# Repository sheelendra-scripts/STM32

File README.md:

# STM32

Compact STM32F103C8T6 controller board designed in KiCad, with USB power and native USB data lines broken out on PA11/PA12. The design includes on-board 3.3 V regulation, external 16 MHz crystal, filtered analog supply (VDDA), BOOT0 selection, and headers for SWD, UART1, and I2C2. Use it as a reference design or a starting point for custom STM32 hardware.

## Highlights

- Complete KiCad project: schematic, PCB, and project files
- Manufacturing-ready outputs (Gerbers, drill files, and pick-and-place)
- 3D model included for enclosure fit checks

## Preview

### 3D View

### PCB Layout

### PCB Schematic

## What is in this repo

- KiCad source files: schematic, PCB, and project settings
- Mechanical model: STEP file for enclosure alignment
- Manufacturing outputs: Gerbers, drill file, and component placement CSVs
- Reference renders: 3D view, layout, and schematic images

## File labels

| File | Label |
| --- | --- |
| [STM32.kicad_sch](STM32.kicad_sch) | Schematic source |
| [STM32.kicad_pcb](STM32.kicad_pcb) | PCB layout source |
| [STM32.kicad_pro](STM32.kicad_pro) | KiCad project settings |
| [STM32.kicad_prl](STM32.kicad_prl) | KiCad local settings |
| [629105150521 (rev1).stp](629105150521%20(rev1).stp) | 3D mechanical model |
| [3D View.png](3D%20View.png) | 3D render |
| [PCB Layout.png](PCB%20Layout.png) | PCB layout render |
| [PCB Schematic.png](PCB%20Schematic.png) | Schematic render |
| [Manufacturing/STM32.csv](Manufacturing/STM32.csv) | Component list export |
| [Manufacturing/STM32-all-pos.csv](Manufacturing/STM32-all-pos.csv) | Pick-and-place positions |
| [Manufacturing/Gerber/](Manufacturing/Gerber/) | Gerber and drill outputs |
| [README.md](README.md) | Project overview |

## Hardware overview

- Power: USB VBUS into AMS1117-3.3 with bulk input/output caps and a power LED
- Clocking: 16 MHz crystal with load capacitors on HSE
- Boot/reset: BOOT0 SPDT switch, pull resistor, and NRST capacitor
- USB: D+ and D- on PA12/PA11 with 1.5 k pull-up on D+
- Debug: 1x4 SWD header (3.3 V, SWDIO, SWCLK, GND)
- IO headers: UART1 and I2C2 (with pull-ups) on 1x4 headers
- Mechanical: four M2 mounting holes

## Schematic description

- Core MCU: STM32F103C8T6 (U2) with dedicated VDD decoupling (multiple 100 nF caps plus a bulk 10 uF). NRST has a 100 nF cap to ground, and BOOT0 is selectable via a small SPDT switch with a pull resistor.
- Clocking: External 16 MHz crystal (Y1) on HSE_IN/HSE_OUT with two 10 pF load capacitors to ground.
- Power supply: USB VBUS feeds an AMS1117-3.3 LDO with 22 uF input/output caps. A red power LED with a series resistor indicates 3.3 V presence.
- Analog supply filtering: VDDA is isolated from 3.3 V using a ferrite bead and local 10 nF + 1 uF caps, plus a 1 uF cap on VDDA.
- USB interface: Micro-USB connector routes D+/D- to PA12/PA11. A 1.5 k pull-up on D+ provides full-speed identification, with VBUS present for USB power/sense.
- Headers: SWD header with 3.3 V, SWDIO, SWCLK, and GND. UART header (USART1 TX/RX) with 3.3 V and GND. I2C header (I2C2 SCL/SDA) with 3.3 V and GND, plus 1.5 k pull-ups.
- Mechanical: Four M2 mounting holes (H1-H4).

## Bill of materials (BOM)

Values are taken from the schematic. Confirm footprints and ratings before ordering.

| Ref(s) | Qty | Value / Part | Notes |
| --- | --- | --- | --- |
| U2 | 1 | STM32F103C8T6 | LQFP-48 MCU |
| U1 | 1 | AMS1117-3.3 | 5 V to 3.3 V LDO |
| Y1 | 1 | 16 MHz crystal | HSE clock |
| C1, C2 | 2 | 22 uF | LDO input/output bulk |
| C3 | 1 | 10 uF | VDD bulk |
| C4, C5, C6, C7 | 4 | 100 nF | VDD decoupling (one per VDD pin) |
| C8 | 1 | 10 nF | VDDA filter |
| C9, C10 | 2 | 1 uF | VDDA filtering |
| C11 | 1 | 100 nF | NRST cap |
| C12, C13 | 2 | 10 pF | Crystal load caps |
| FB1 | 1 | Ferrite bead, 120 R | VDDA filter |
| D1 | 1 | Red LED | Power indicator |
| R1 | 1 | 1.5 k | LED series resistor |
| R2 | 1 | 10 k | BOOT0 pull |
| R3 | 1 | 1.5 k | USB D+ pull-up |
| R4, R5 | 2 | 1.5 k | I2C pull-ups |
| SW1 | 1 | SPDT switch | BOOT0 select |
| J1 | 1 | Micro-USB B receptacle | USB + power |
| J2 | 1 | 1x4 header | UART1 header |
| J3 | 1 | 1x4 header | SWD header |
| J4 | 1 | 1x4 header | I2C2 header |
| H1, H2, H3, H4 | 4 | M2 mounting holes | Mechanical |

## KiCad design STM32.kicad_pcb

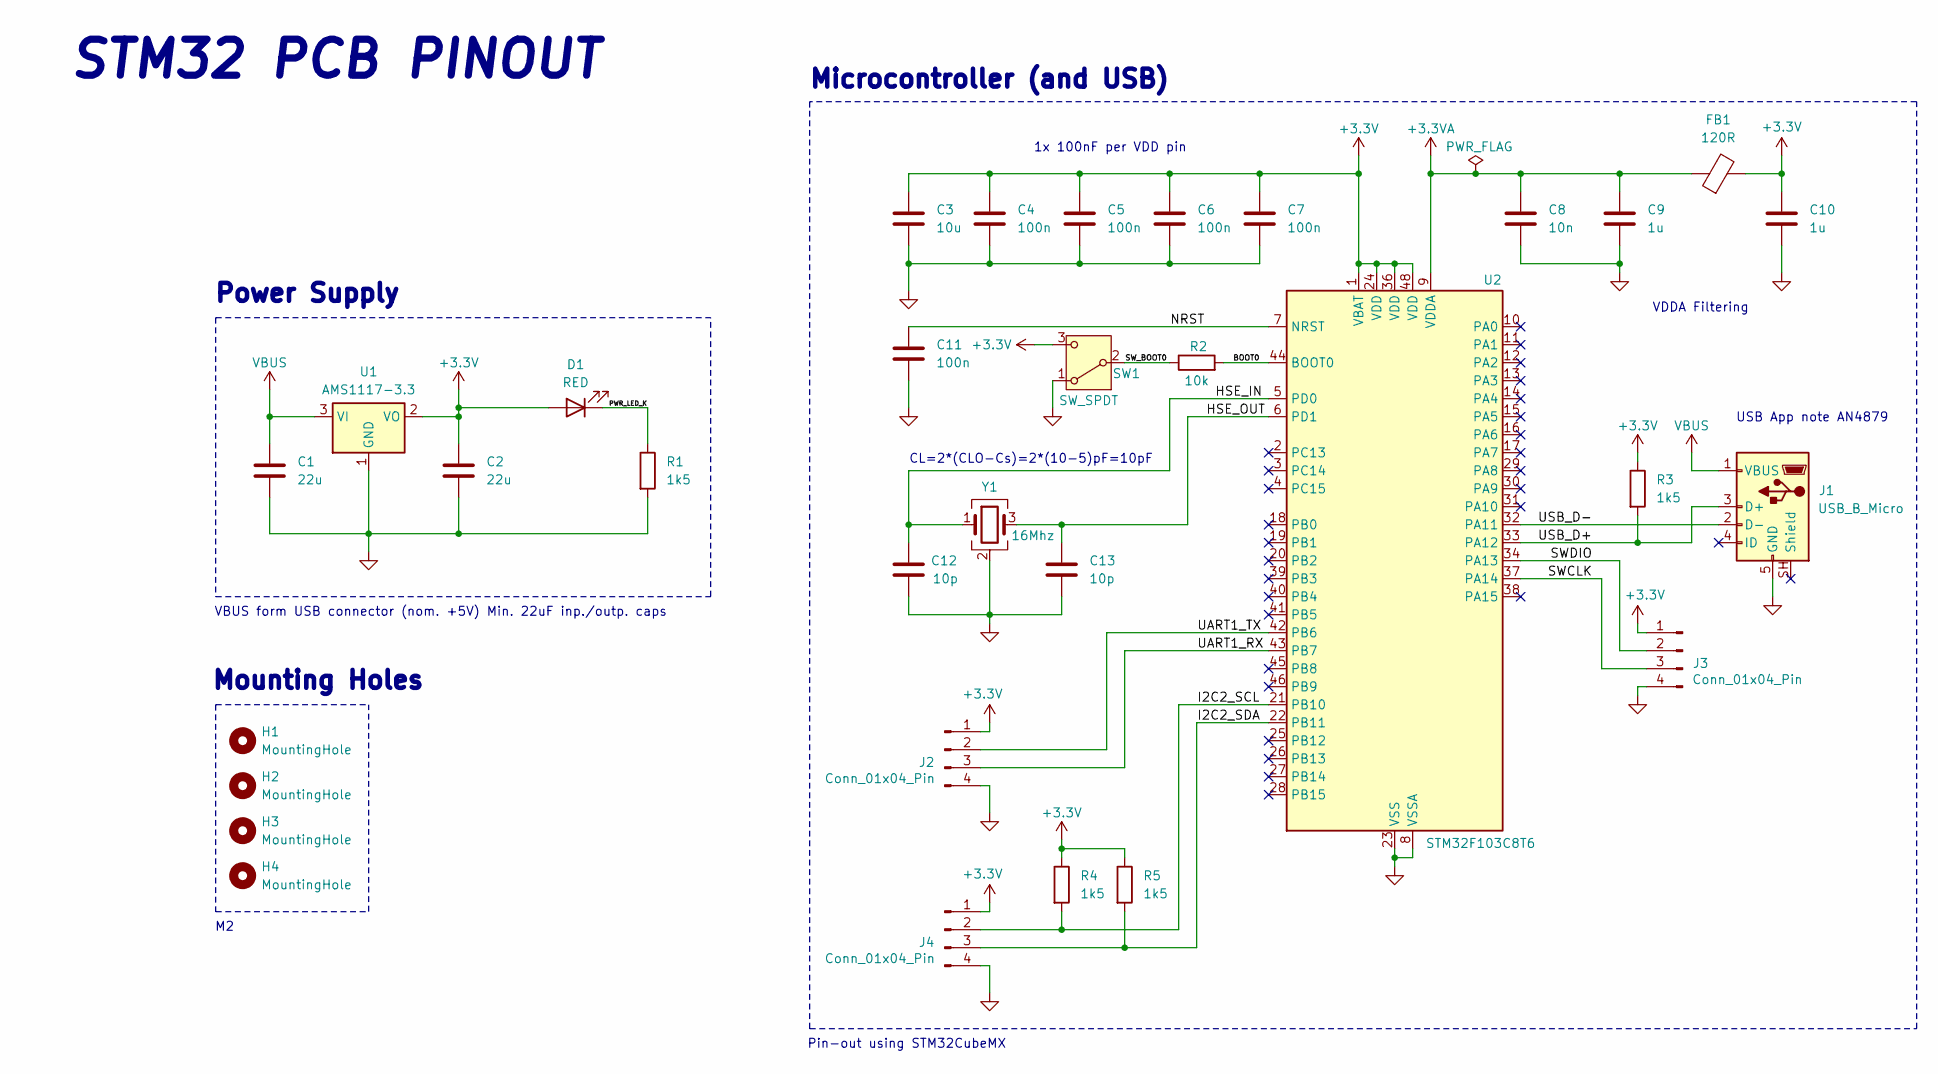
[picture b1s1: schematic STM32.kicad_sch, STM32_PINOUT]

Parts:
C1: 22u; C_0402_1005Metric
C2: 22u; C_0805_2012Metric
C3: 10u; C_0603_1608Metric
C4, C5, C6, C7, C11: 100n; C_0402_1005Metric
C8: 10n; C_0402_1005Metric
C9, C10: 1u; C_0402_1005Metric
C12, C13: 10p; C_0402_1005Metric
D1: RED; LED_0603_1608Metric
FB1: 120R; L_0603_1608Metric
H1, H2, H3, H4: MountingHole; MountingHole_2.2mm_M2
J1: USB_B_Micro; USB_Micro-B_Wuerth_629105150521
J2, J3, J4: Conn_01x04_Pin; PinHeader_1x04_P2.54mm_Vertical
R1, R3, R4, R5: 1k5; R_0402_1005Metric
R2: 10k; R_0402_1005Metric
SW1: SW_SPDT; SW_SPDT_PCM12
U1: AMS1117-3.3; SOT-223-3_TabPin2
U2: STM32F103C8T6; LQFP-48_7x7mm_P0.5mm
Y1: 16Mhz; Crystal_SMD_3225-4Pin_3.2x2.5mm

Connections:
+3.3V: C2.1, C3.1, C4.1, C5.1, C6.1, C7.1, C10.1, D1.2 (A), FB1.2, J2.1, J3.1, J4.1, R3.1, R4.1, R5.1, SW1.3 (C), U1.2 (VO), U2.1 (VBAT), U2.24 (VDD), U2.36 (VDD), U2.48 (VDD)
+3.3VA: C8.1, C9.1, FB1.1, U2.9 (VDDA)
/BOOT0: R2.2, U2.44 (BOOT0)
/HSE_IN: C12.1, U2.5 (PD0), Y1.1
/HSE_OUT: C13.1, U2.6 (PD1), Y1.3
/I2C2_SCL: J4.2, R4.2, U2.21 (PB10)
/I2C2_SDA: J4.3, R5.2, U2.22 (PB11)
/NRST: C11.1, U2.7 (NRST)
/PWR_LED_K: D1.1 (K), R1.1
/SWCLK: J3.3, U2.37 (PA14)
/SWDIO: J3.2, U2.34 (PA13)
/SW_BOOT0: R2.1, SW1.2 (B)
/UART1_RX: J2.3, U2.43 (PB7)
/UART1_TX: J2.2, U2.42 (PB6)
/USB_D+: J1.3 (D+), R3.2, U2.33 (PA12)
/USB_D-: J1.2 (D-), U2.32 (PA11)
GND: C1.2, C2.2, C3.2, C4.2, C5.2, C6.2, C7.2, C8.2, C9.2, C10.2, C11.2, C12.2, C13.2, J1.5 (GND), J2.4, J3.4, J4.4, R1.2, SW1.1 (A), U1.1 (GND), U2.8 (VSSA), U2.23 (VSS), U2.35 (VSS), U2.47 (VSS), Y1.2 (G), Y1.4 (G)
VBUS: C1.1, J1.1 (VBUS), U1.3 (VI)

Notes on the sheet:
STM32 PCB PINOUT
USB App note AN4879
VDDA Filtering
Microcontroller (and USB)
Pin-out using STM32CubeMX
CL=2*(CLO-Cs)=2*(10-5)pF=10pF
Power Supply
VBUS form USB connector (nom. +5V) Min. 22uF inp./outp. caps
1x 100nF per VDD pin
Mounting Holes

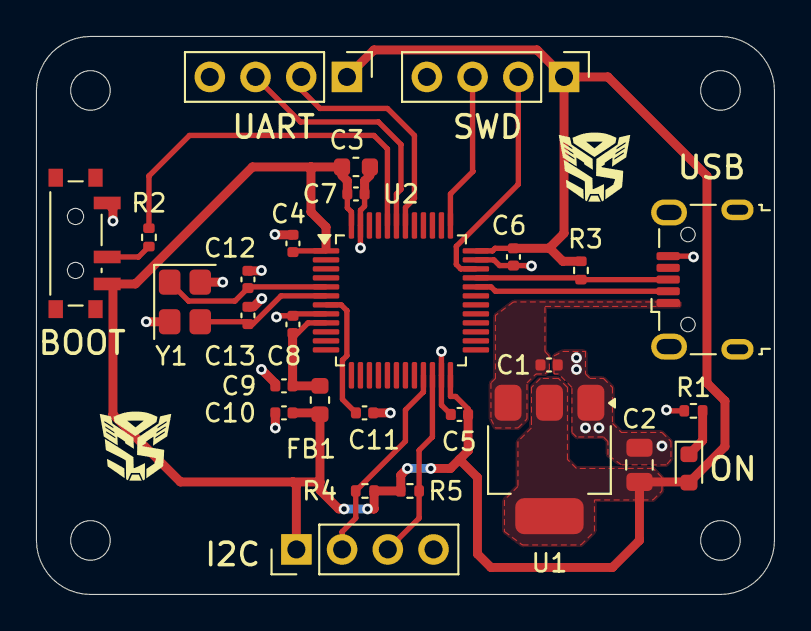
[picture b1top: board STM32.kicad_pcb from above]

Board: 2 copper layers, 41.0 x 31.0 mm, 32 parts (0 on the bottom side), 18 nets.

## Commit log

2026-05-25 added files
2026-05-25 added lables
